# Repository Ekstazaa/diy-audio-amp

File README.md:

# diy-audio-amp
This is a modular analog audio amplifier project designed for educational and hobby use. It is composed of clearly separated functional blocks such as input stage, voltage amplification, output stage, and power supply – making it easy to understand, modify, or reuse in other designs.

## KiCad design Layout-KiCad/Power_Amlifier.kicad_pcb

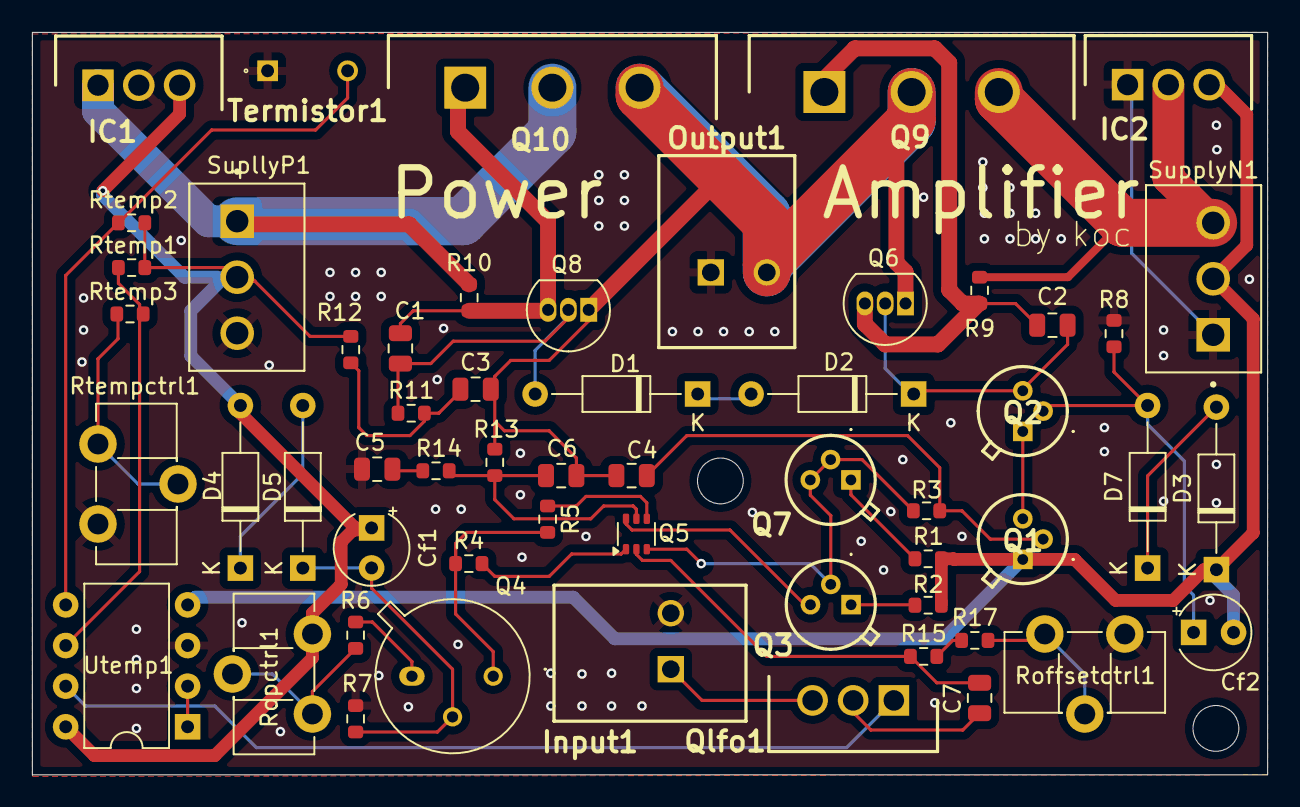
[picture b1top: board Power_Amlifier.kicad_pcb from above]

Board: 2 copper layers, 77.2 x 46.4 mm, 56 parts (0 on the bottom side), 39 nets.

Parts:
C1, C2: 100p; C_0805_2012Metric
C3, C5: 10u; C_0805_2012Metric
C4: 470p; C_0805_2012Metric
C6: 2p2; C_0805_2012Metric
C7: 1.5n; C_0805_2012Metric
Cf1, Cf2: 100u; CP_Radial_Tantal_D4.5mm_P2.50mm
D1, D2, D3, D4, D5, D7: 1N914; D_DO-35_SOD27_P10.16mm_Horizontal
IC1, IC2: L7824CV; TO255P460X1020X2008-3P
Input1: 250-102; 250102
Output1: 250-102; 250102
Q1, Q2, Q3, Q7: 2N2484
Q4: BC303; TO-39-3
Q5: BC856BS; SOT-363_SC-70-6
Q6: Q_PNP_EBC; TO-92_Inline
Q8: Q_NPN_EBC; TO-92_Inline
Q9: 2SC5200-O_Q_; TO545P520X2000X2900-3P
Q10: 2SA1943-O_Q_; TO545P520X2050X2650-3P
Qlfo1: IRFZ34NPBF; TO254P469X1042X1967-3P
R1, R2: 220; R_0603_1608Metric
R3: 1; R_0603_1608Metric
R4, R5: 100; R_0603_1608Metric
R6, R9, R10: 330; R_0603_1608Metric
R7, R11, R12, R17: 10k; R_0603_1608Metric
R8: 470k; R_0603_1608Metric
R13: 220k; R_0603_1608Metric
R14: 11k; R_0603_1608Metric
R15: 200k; R_0603_1608Metric
Roffsetctrl1: R20k; Potentiometer_ACP_CA9-H5_Horizontal
Ropctrl1: R1k; Potentiometer_ACP_CA9-H5_Horizontal
Rtemp1, Rtemp2: 47k; R_0603_1608Metric
Rtemp3: 5k; R_0603_1608Metric
Rtempctrl1: R10k; Potentiometer_ACP_CA9-H5_Horizontal
SupllyP1: TBP03R2-350-03BE; CUI_TBP03R2-350-03BE
SupplyN1: TBP03R2-350-03BE; CUI_TBP03R2-350-03BE
Termistor1: B57164K0103K000; B57164K_K164
Utemp1: Opamp_Dual; DIP-8_W7.62mm

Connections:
+24V: Cf1.1, D4.2 (A), IC1.3 (OUTPUT), R12.2, Ropctrl1.3, Rtemp1.2, Rtemp2.2, SupllyP1.2, Utemp1.8 (V+)
+30V: IC1.1 (INPUT), Q10.2 (COLLECTOR_(HEAT_SINK)), R10.2, SupllyP1.1
-24V: Cf2.2, D3.1 (K), IC2.3 (OUTPUT), Q1.1 (E), R1.1, R2.1, SupplyN1.2, Utemp1.4 (V-)
-30V: IC2.2 (GROUND), Q9.3 (E), R9.1, SupplyN1.3
GND: C5.1, IC1.2 (GROUND), IC2.1 (INPUT), Input1.2, Output1.1, R7.1, R8.2, Roffsetctrl1.1, Rtempctrl1.3, SupllyP1.3, SupplyN1.1, Termistor1.1, Utemp1.3 (+)
unnamed: C3.1, R11.2, R12.1
unnamed: C5.2, R14.2
unnamed: C1.1, D1.2 (A), Q8.2 (B), R11.1
unnamed: D1.1 (K), D2.2 (A)
unnamed: C2.1, D2.1 (K), Q2.3 (C), Q6.2 (B)
unnamed: D3.2 (A), D7.1 (K)
unnamed: D4.1 (K), D5.2 (A)
unnamed: Cf1.2, D5.1 (K), Q4.2 (B), R7.2
unnamed: Cf2.1, D7.2 (A), Q2.2 (B), R8.1
unnamed: C4.1, Q1.2 (B), R3.1
unnamed: Q1.3 (C), Q2.1 (E)
unnamed: Q3.2 (B), Q5.3 (C2), Q7.2 (B), Q7.3 (C), R3.2
unnamed: Q3.3 (C), Q5.6 (C1)
unnamed: Q3.1 (E), R2.2
unnamed: Q4.3 (C), R4.1, R5.2
unnamed: Q4.1 (E), R6.1
unnamed: C7.2, Q5.2 (B1), R15.1
unnamed: Q5.1 (E1), R4.2
unnamed: C6.1, Q5.5 (B2), R13.2, R14.1
unnamed: Q5.4 (E2), R5.1
unnamed: C2.2, Q6.3 (C), Q9.1 (B), R9.2
unnamed: Q7.1 (E), R1.2
unnamed: C1.2, Q8.3 (C), Q10.1 (BASE), R10.1
unnamed: C3.2, C4.2, C6.2, Output1.2, Q6.1 (E), Q8.1 (E), Q9.2 (C), Q10.3 (EMITTER), R13.1
unnamed: C7.1, Qlfo1.2 (D)
unnamed: Input1.1, Qlfo1.3 (S)
unnamed: R6.2, Ropctrl1.1, Ropctrl1.2
unnamed: R15.2, R17.1
unnamed: R17.2, Roffsetctrl1.2, Roffsetctrl1.3
unnamed: Rtemp3.2, Rtempctrl1.1, Rtempctrl1.2
unnamed: Utemp1.1, Utemp1.2 (-)
unnamed: Rtemp2.1, Termistor1.2, Utemp1.5 (+)
unnamed: Rtemp1.1, Rtemp3.1, Utemp1.6 (-)
Vcntrl: Qlfo1.1 (G), Utemp1.7

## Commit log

2025-05-29 Update design-notes.md
    added theory of output stage
2025-05-31 Update design-notes.md
    description of added resistors and transistors
2025-06-01 Update design-notes.md
    resumalte with realistic current source
2025-06-01 Create output_stage_tran_tb
    tb for output stage
2025-06-01 Create output_stage_tran_tb
2025-06-01 Update design-notes.md
    added ac screenshots
2025-06-01 Rename BC556.PDF to BC556_BC557.PDF
2025-06-02 testbench of input stage + vas
2025-07-08 Layout of amplifier
2025-08-10 Update design-notes.md
    added slew rate and cmrr
2025-08-11 Update design-notes.md
    added summary
2025-08-23 Update design-notes.md
    added Bibliography
2025-08-23 added files of amplifer's pcb
2025-08-24 Update design-notes.md
    added short explain of VAS and added future subsections
